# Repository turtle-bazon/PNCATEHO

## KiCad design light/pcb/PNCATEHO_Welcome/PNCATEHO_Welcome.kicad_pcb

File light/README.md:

# PNCATEHO

## PNCATEHO Welcome

### BOM

[IBOM](https://htmlpreview.github.io/?https://github.com/turtle-bazon/PNCATEHO/blob/master/light/ibom_welcome.html)

| Name               | Value          | Package                            | Quanity | JLC                                                                                    | Aliexpress                                                          | Misc                                                                                                                             |
| ------------------ | -------------- | :--------------------------------- | ------- | -------------------------------------------------------------------------------------- | ------------------------------------------------------------------- | -------------------------------------------------------------------------------------------------------------------------------- |
| Capacitor          | 1              | 0805                               | 11      | [JLCPCB](https://jlcpcb.com/partdetail/39123-0805B104K500NT/C38141)                    | [Aliexpress](https://aliexpress.ru/item/1005008523091680.html)      |                                                                                                                                  |
| Capacitor          | 1uF            | 0805                               | 4       | [JLCPCB](https://jlcpcb.com/partdetail/29074-CL21B105KBFNNNE/C28323)                   | [Aliexpress](https://aliexpress.ru/item/1005008523091680.html)      |                                                                                                                                  |
| Capacitor          | 20pF           | 0805                               | 2       | [JLCPCB](https://jlcpcb.com/partdetail/KEMET-C0402C200K4GAC7867/C3839897)              | [Aliexpress](https://aliexpress.ru/item/1005008523091680.html)      |                                                                                                                                  |
| Resitor            | 1k             | 0805                               | 4       | [JLCPCB](https://jlcpcb.com/partdetail/VO-0805_1_1K/C2889437)                          | [Aliexpress](https://aliexpress.ru/item/1005004542788613.html)<br>  |                                                                                                                                  |
| Resitor            | 5.1k           | 0805                               | 2       | [JLCPCB](https://jlcpcb.com/partdetail/C5123602)                                       | [Aliexpress](https://aliexpress.ru/item/1005004542788613.html)<br>  |                                                                                                                                  |
| Resitor            | 27Ω            | 0805                               | 2       | [JLCPCB](https://jlcpcb.com/partdetail/YAGEO-AC0805FR7W27RL/C5120098)                  | [Aliexpress](https://aliexpress.ru/item/1005004542788613.html)<br>  |                                                                                                                                  |
| Resitor            | 10k            | 0805                               | 1       | [JLCPCB](https://jlcpcb.com/partdetail/VO-0805_1_10K/C2889436)                         | [Aliexpress](https://aliexpress.ru/item/1005004542788613.html)<br>  |                                                                                                                                  |
| LED                | Red            | 0805                               | 1       | [JLCPCB](https://jlcpcb.com/partdetail/85425-NCD0805R1/C84256)                         | [Aliexpress](https://aliexpress.ru/item/4000936781234.html)         |                                                                                                                                  |
| LED                | Blue           | 0805                               | 1       | [JLCPCB](https://jlcpcb.com/partdetail/Hubei_KentoElec-C2293/C2293)                    | [Aliexpress](https://aliexpress.ru/item/4000936781234.html)         |                                                                                                                                  |
| LED                | WS2812B        | 2020                               | 20      | [JLCPCB](https://jlcpcb.com/partdetail/Worldsemi-WS2812B2020/C965555)                  | [Aliexpress](https://aliexpress.ru/item/1005005812058130.html)<br>  |                                                                                                                                  |
| LDO                | RT9013-33GB    | SOT23-5                            | 1       | [JLCPCB](https://jlcpcb.com/partdetail/RichtekTech-RT901333GB/C47773)                  | [Aliexpress](https://aliexpress.ru/item/1005009379057215.html)<br>  |                                                                                                                                  |
| FLASH              | W25Q32JVSSIQ   | SOIC-8-208mil                      | 1       | [JLCPCB](https://jlcpcb.com/partdetail/WinbondElec-W25Q32JVSSIQ/C179173)<br>           | [Aliexpress](https://ali.click/ja3ym8)                              |                                                                                                                                  |
| ESD                | USBLC6-2SC6    | SOT23-6                            | 1       | [JLCPCB](https://jlcpcb.com/partdetail/STMicroelectronics-USBLC62SC6/C7519)<br>        | [Aliexpress](https://ali.click/vl3ymq)                              |                                                                                                                                  |
| Crystal            | 12MHz 20pF     | SMD3225-4P                         | 1       | [JLCPCB](https://jlcpcb.com/partdetail/YXC_CrystalOscillators-X322512MSB4SI/C9002)<br> | [Aliexpress](https://aliexpress.ru/item/1005006861125810.html)      |                                                                                                                                  |
| Fuse               | 500mA 6V       | 0805                               | 1       | [JLCPCB](https://jlcpcb.com/partdetail/BHFUSE-BSMD0805_0506V/C883108)<br>              | [Aliexpress](https://aliexpress.ru/item/1005009503064953.html)      |                                                                                                                                  |
| MCU                | RP2040         | LQFN-56(7x7)                       | 1       | [JLCPCB](https://jlcpcb.com/partdetail/RaspberryPi-RP2040/C2040)<br>                   | [Aliexpress](https://aliexpress.ru/item/1005007523217221.html?)     |                                                                                                                                  |
| Type-C             | TYPE-C-31-M-12 | 16P 5A Female                      | 1       | [JLCPCB](https://jlcpcb.com/partdetail/Korean_HropartsElec-TYPE_C_31_M12/C165948)<br>  | [Aliexpress](https://aliexpress.ru/item/1005005260008476.html?)<br> |                                                                                                                                  |
| Tactile Switch     | TS342A2P       | SMD 4x3mm                          | 2       | [JLCPCB](https://jlcpcb.com/partdetail/SHOUHAN-TS342A2P/C398055)                       | [Aliexpress](https://ali.click/1z4ym0l)<br>                         |                                                                                                                                  |
| Swtiches           | PG1316S        | SMD                                | 10      | [JLCPCB](https://jlcpcb.com/partdetail/Kailh-CPG1316S01D02/C42372112)<br>              |                                                                     | [Kailh](https://www.kailhswitch.com/mechanical-keyboard-switches/low-profile-key-switches/kailh-ultra-thin-notebook-switch.html) |
| Sockets (Optional) | PBS            | PH8.5                              | 10 pin  |                                                                                        | [Aliexpress](https://aliexpress.ru/item/1005001621924231.html)<br>  |                                                                                                                                  |
| Pin (Optional)     | PLS            |                                    | 10 Pin  |                                                                                        | [Aliexpress](https://aliexpress.ru/item/1005001708024520.html)<br>  |                                                                                                                                  |
| JST (Optional)     | SM10B-GHS-TB   | P=1.25mm,Surface Mount，Right Angle | 2       | [JLCPCB](https://jlcpcb.com/partdetail/JST-SM10B_GHSTB/C2683602)<br>                   | <br>                                                                | [ChipDip](https://www.chipdip.ru/product/sm10b-ghs-tb-connector-header-surface-mount-right-angle-jst-8033862895)                 |

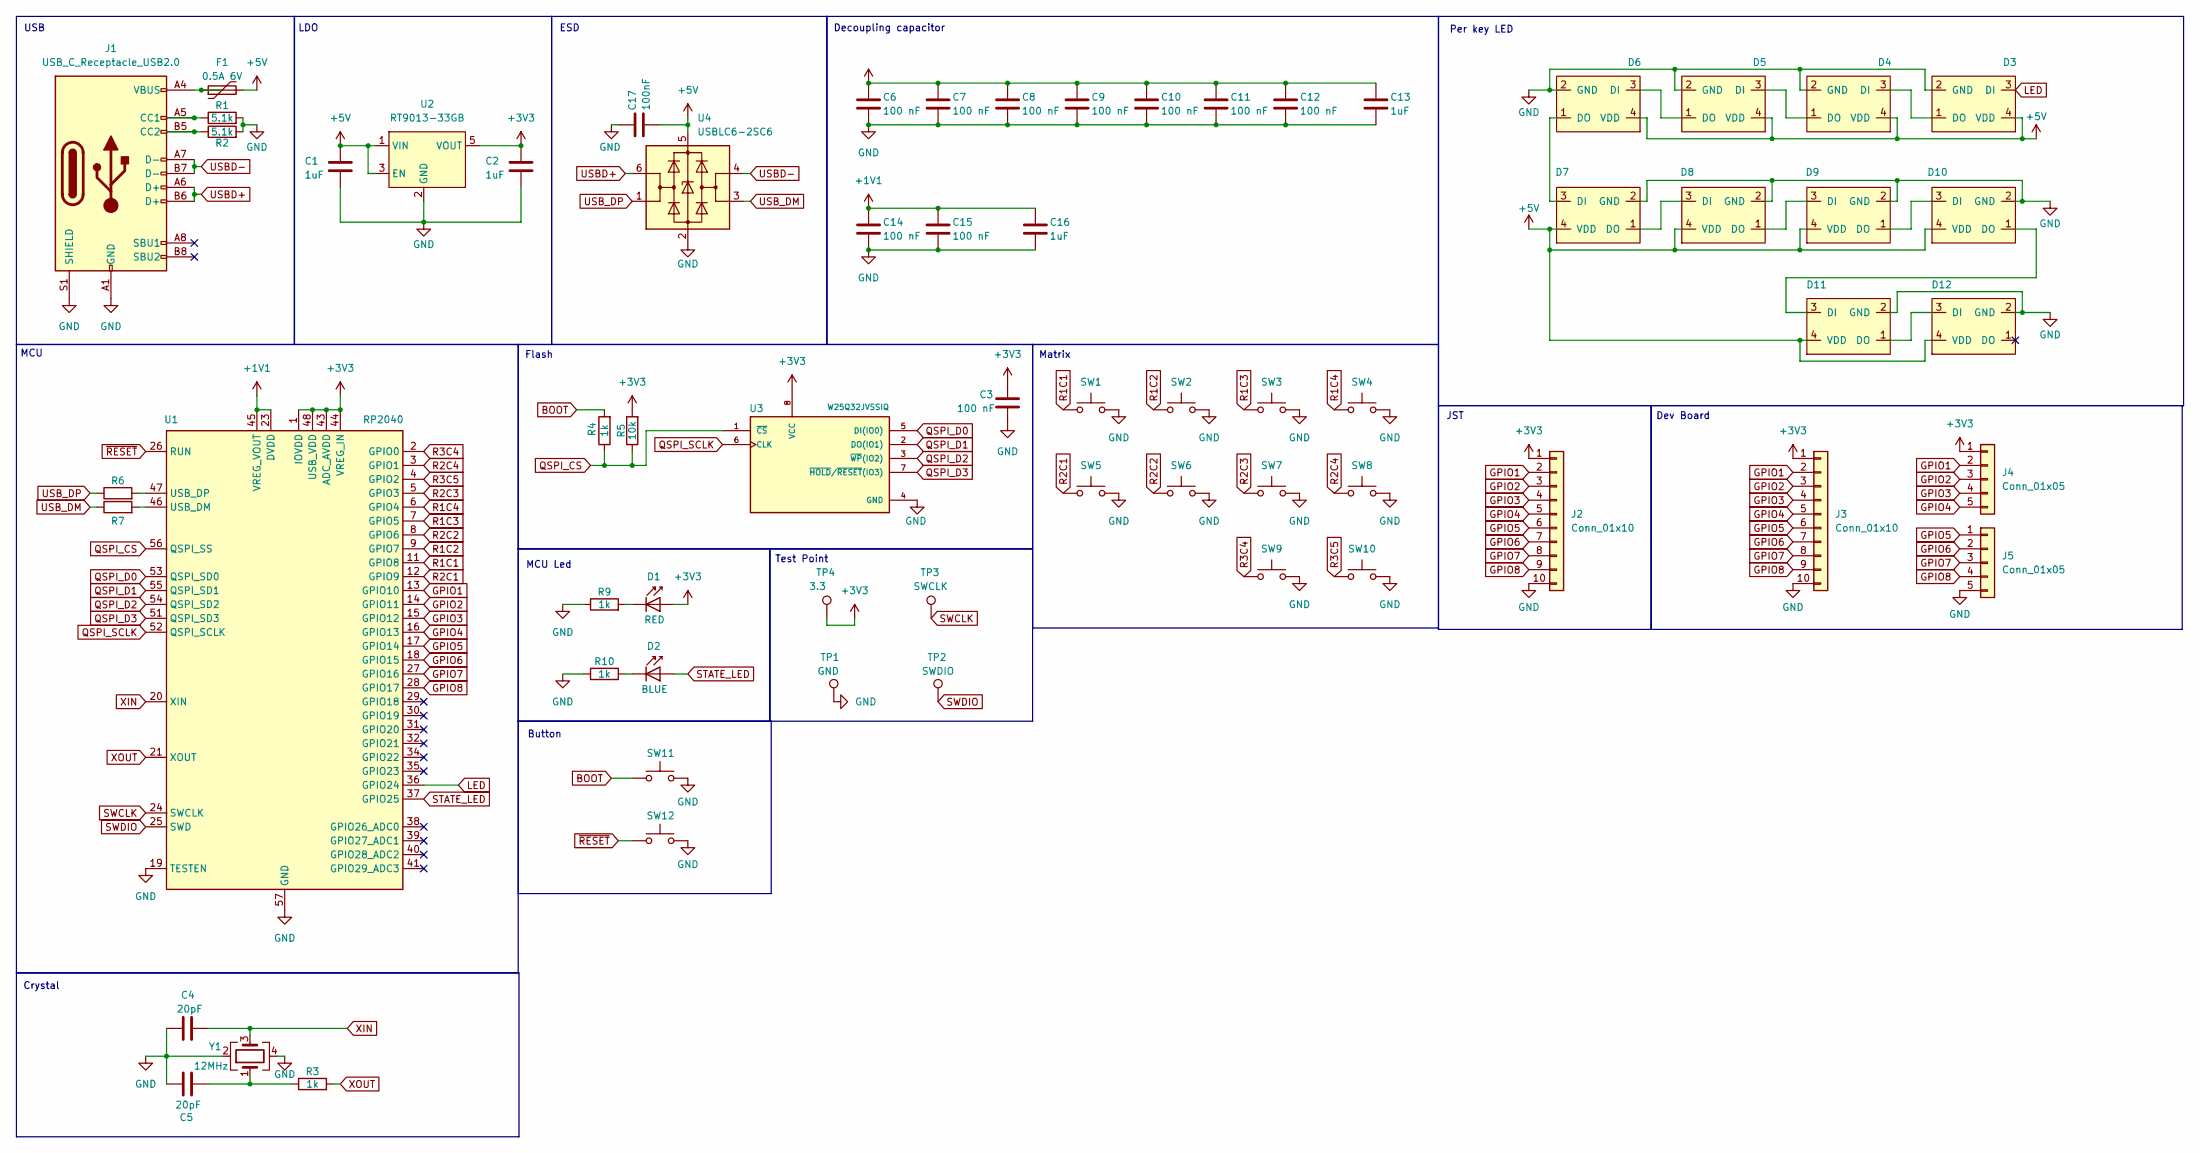
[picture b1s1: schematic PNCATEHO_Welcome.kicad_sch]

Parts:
C1, C2, C13, C16: 1uF; C_0805_2012Metric_Pad1.18x1.45mm_HandSolder
C3, C6, C7, C8, C9, C10, C11, C12, C14, C15: 100 nF; C_0805_2012Metric_Pad1.18x1.45mm_HandSolder
C4, C5: 20pF; C_0805_2012Metric_Pad1.18x1.45mm_HandSolder
C17: 100nF; C_0805_2012Metric_Pad1.18x1.45mm_HandSolder
D1: RED; LED_0805_2012Metric_Pad1.15x1.40mm_HandSolder
D2: BLUE; LED_0805_2012Metric_Pad1.15x1.40mm_HandSolder
D3, D4, D5, D6, D7, D8, D9, D10, D11, D12: WS2812-2020-2.00mmx2.20mm
F1: 0.5А 6V; Fuse_0805_2012Metric_Pad1.15x1.40mm_HandSolder
J1: USB_C_Receptacle_USB2.0; USB_C_Receptacle_TYPE-C-31-M-12
J2, J3: Conn_01x10; JST_GH_SM10B-GHS-TB_1x10-1MP_P1.25mm_Horizontal
J4, J5: Conn_01x05; PinHeader_1x05_P2.54mm_Vertical
R1, R2: 5.1k; R_0805_2012Metric_Pad1.20x1.40mm_HandSolder
R3, R4, R9, R10: 1k; R_0805_2012Metric_Pad1.20x1.40mm_HandSolder
R5: 10k; R_0805_2012Metric_Pad1.20x1.40mm_HandSolder
R6, R7: 27; R_0805_2012Metric_Pad1.20x1.40mm_HandSolder
SW1, SW2, SW3, SW4, SW5, SW6, SW7, SW8, SW9, SW10: SW_PG1316
SW11: Boot; SW_PUSH
SW12: Reset; SW_PUSH
TP1: GND; TestPoint_Pad_1.0x1.0mm
TP2: SWDIO; TestPoint_Pad_D1.0mm
TP3: SWCLK; TestPoint_Pad_D1.0mm
TP4: 3.3; TestPoint_Pad_D1.0mm
U1: RP2040; QFN-56-1EP_7x7mm_P0.4mm_EP3.2x3.2mm_ThermalVias
U2: RT9013-33GB; SOT-23-5_HandSoldering
U3: W25Q32JVSSIQ; SOIC-8_5.3x5.3mm_P1.27mm; M_PART_NUMBER W25QXX
U4: USBLC6-2SC6; SOT-23-6_Handsoldering
Y1: 12MHz; Crystal_SMD_3225-4Pin_3.2x2.5mm_HandSoldering

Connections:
+1V1: C14.1, C15.1, C16.1, U1.23 (DVDD), U1.45 (VREG_VOUT), U1.50 (DVDD)
+3V3: C2.1, C3.1, C6.1, C7.1, C8.1, C9.1, C10.1, C11.1, C12.1, C13.1, D1.2 (A), J2.1, J3.1, J4.1, R5.2, TP4.1, U1.1 (IOVDD), U1.10 (IOVDD), U1.22 (IOVDD), U1.33 (IOVDD), U1.42 (IOVDD), U1.43 (ADC_AVDD), U1.44 (VREG_IN), U1.48 (USB_VDD), U1.49 (IOVDD), U2.5 (VOUT), U3.8 (VCC)
+5V: C1.1, C17.2, D3.4 (VDD), D4.4 (VDD), D5.4 (VDD), D6.4 (VDD), D7.4 (VDD), D8.4 (VDD), D9.4 (VDD), D10.4 (VDD), D11.4 (VDD), D12.4 (VDD), F1.2, U2.1 (VIN), U2.3 (EN), U4.5 (VBUS)
BOOT: R4.2, SW11.2
GND: C1.2, C2.2, C3.2, C4.2, C5.2, C6.2, C7.2, C8.2, C9.2, C10.2, C11.2, C12.2, C13.2, C14.2, C15.2, C16.2, C17.1, D3.2 (GND), D4.2 (GND), D5.2 (GND), D6.2 (GND), D7.2 (GND), D8.2 (GND), D9.2 (GND), D10.2 (GND), D11.2 (GND), D12.2 (GND), J1.A1 (GND), J1.A12 (GND), J1.B1 (GND), J1.B12 (GND), J1.S1 (SHIELD), J2.10, J3.10, J5.5, R1.2, R2.2, R9.1, R10.1, SW1.2, SW2.2, SW3.2, SW4.2, SW5.2, SW6.2, SW7.2, SW8.2, SW9.2, SW10.2, SW11.1, SW12.1, TP1.1, U1.19 (TESTEN), U1.57 (GND), U2.2 (GND), U3.4 (GND), U4.2 (GND), Y1.2, Y1.4
GPIO1: J2.2, J3.2, J4.2, U1.13 (GPIO10)
GPIO2: J2.3, J3.3, J4.3, U1.14 (GPIO11)
GPIO3: J2.4, J3.4, J4.4, U1.15 (GPIO12)
GPIO4: J2.5, J3.5, J4.5, U1.16 (GPIO13)
GPIO5: J2.6, J3.6, J5.1, U1.17 (GPIO14)
GPIO6: J2.7, J3.7, J5.2, U1.18 (GPIO15)
GPIO7: J2.8, J3.8, J5.3, U1.27 (GPIO16)
GPIO8: J2.9, J3.9, J5.4, U1.28 (GPIO17)
LED: D3.3 (DI), U1.36 (GPIO24)
unnamed: C5.1, R3.1, Y1.1
unnamed: D1.1 (K), R9.2
unnamed: D2.1 (K), R10.2
unnamed: D3.1 (DO), D4.3 (DI)
unnamed: D4.1 (DO), D5.3 (DI)
unnamed: D5.1 (DO), D6.3 (DI)
unnamed: D6.1 (DO), D7.3 (DI)
unnamed: D7.1 (DO), D8.3 (DI)
unnamed: D8.1 (DO), D9.3 (DI)
unnamed: D9.1 (DO), D10.3 (DI)
unnamed: D10.1 (DO), D11.3 (DI)
unnamed: D11.1 (DO), D12.3 (DI)
unnamed: F1.1, J1.A4 (VBUS), J1.A9 (VBUS), J1.B4 (VBUS), J1.B9 (VBUS)
unnamed: J1.A5 (CC1), R1.1
unnamed: J1.B5 (CC2), R2.1
unnamed: R7.2, U1.46 (USB_DM)
unnamed: R6.2, U1.47 (USB_DP)
QSPI_CS: R4.1, R5.1, U1.56 (QSPI_SS), U3.1 (~CS)
QSPI_D0: U1.53 (QSPI_SD0), U3.5 (DI(IO0))
QSPI_D1: U1.55 (QSPI_SD1), U3.2 (DO(IO1))
QSPI_D2: U1.54 (QSPI_SD2), U3.3 (~WP(IO2))
QSPI_D3: U1.51 (QSPI_SD3), U3.7 (~HOLD/~RESET(IO3))
QSPI_SCLK: U1.52 (QSPI_SCLK), U3.6 (CLK)
R1C1: SW1.1, U1.11 (GPIO8)
R1C2: SW2.1, U1.9 (GPIO7)
R1C3: SW3.1, U1.7 (GPIO5)
R1C4: SW4.1, U1.6 (GPIO4)
R2C1: SW5.1, U1.12 (GPIO9)
R2C2: SW6.1, U1.8 (GPIO6)
R2C3: SW7.1, U1.5 (GPIO3)
R2C4: SW8.1, U1.3 (GPIO1)
R3C4: SW9.1, U1.2 (GPIO0)
R3C5: SW10.1, U1.4 (GPIO2)
STATE_LED: D2.2 (A), U1.37 (GPIO25)
SWCLK: TP3.1, U1.24 (SWCLK)
SWDIO: TP2.1, U1.25 (SWD)
USBD+: J1.A6 (D+), J1.B6 (D+), U4.6 (I/O1)
USBD-: J1.A7 (D-), J1.B7 (D-), U4.4 (I/O2)
USB_DM: R7.1, U4.3 (I/O2)
USB_DP: R6.1, U4.1 (I/O1)
XIN: C4.1, U1.20 (XIN), Y1.3
XOUT: R3.2, U1.21 (XOUT)
~RESET: SW12.2, U1.26 (RUN)

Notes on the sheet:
ESD
Test Point
Per key LED
MCU Led
Dev Board
Crystal
USB
MCU
Flash
LDO
Decoupling capacitor
JST
Button
Matrix

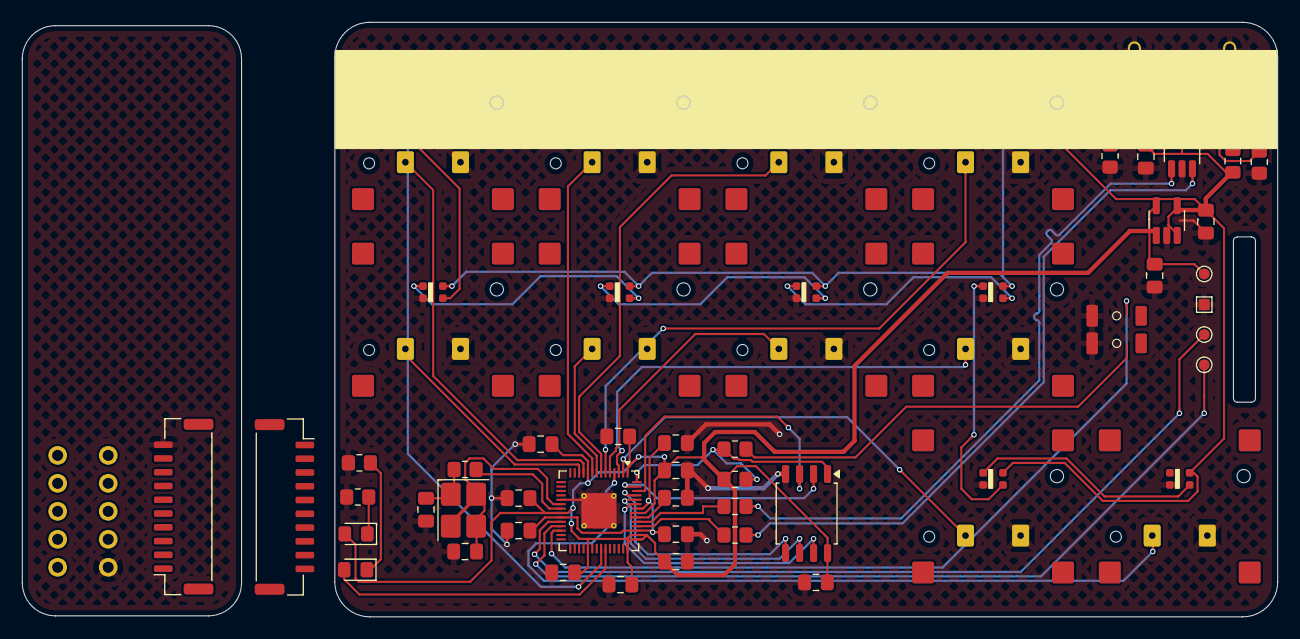
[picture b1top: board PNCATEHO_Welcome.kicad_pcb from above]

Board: 2 copper layers, 85.6 x 54.0 mm, 65 parts (0 on the bottom side), 57 nets.

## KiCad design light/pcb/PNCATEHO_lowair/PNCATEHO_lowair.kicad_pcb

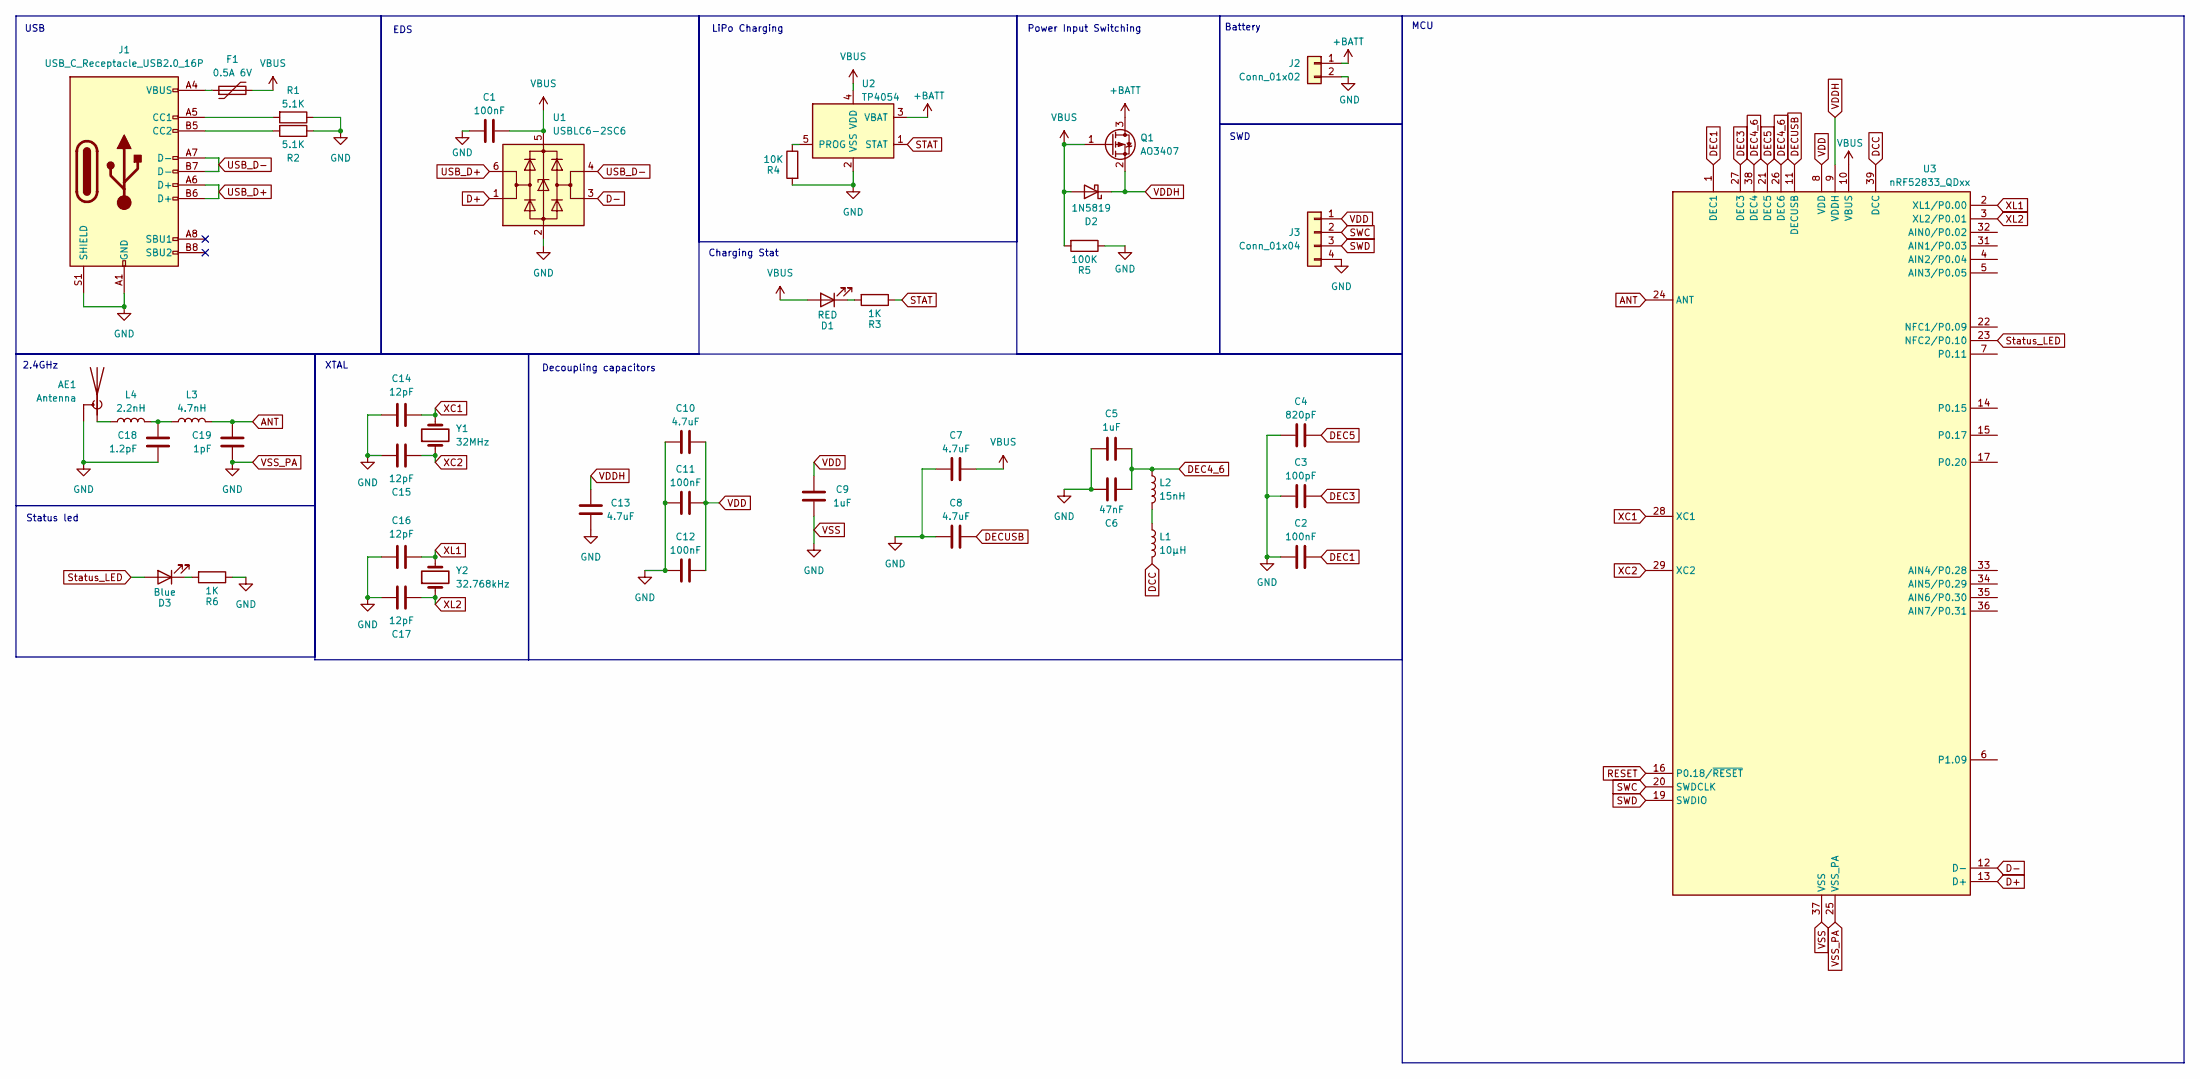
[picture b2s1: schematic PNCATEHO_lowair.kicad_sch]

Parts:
AE1: Antenna; Texas_SWRA117D_2.4GHz_Left
C1, C2, C11, C12: 100nF; C_0201_0603Metric_Pad0.64x0.40mm_HandSolder
C3: 100pF; C_0201_0603Metric_Pad0.64x0.40mm_HandSolder
C4: 820pF; C_0201_0603Metric_Pad0.64x0.40mm_HandSolder
C5, C9: 1uF; C_0402_1005Metric_Pad0.74x0.62mm_HandSolder
C6: 47nF; C_0201_0603Metric_Pad0.64x0.40mm_HandSolder
C7, C8, C10, C13: 4.7uF; C_0603_1608Metric_Pad1.08x0.95mm_HandSolder
C14, C15, C16, C17: 12pF; C_0201_0603Metric_Pad0.64x0.40mm_HandSolder
C18: 1.2pF; C_0201_0603Metric_Pad0.64x0.40mm_HandSolder
C19: 1pF; C_0201_0603Metric_Pad0.64x0.40mm_HandSolder
D1: RED; LED_0805_2012Metric_Pad1.15x1.40mm_HandSolder
D2: 1N5819; D_SOD-323_HandSoldering
D3: Blue; LED_0805_2012Metric_Pad1.15x1.40mm_HandSolder
F1: 0.5А 6V; Fuse_1206_3216Metric_Pad1.42x1.75mm_HandSolder
J1: USB_C_Receptacle_USB2.0_16P; USB_C_Receptacle_TYPE-C-31-M-12
J2: Conn_01x02
J3: Conn_01x04; connector_swd_REV
L1: 10μH; L_0603_1608Metric_Pad1.05x0.95mm_HandSolder
L2: 15nH; L_0402_1005Metric_Pad0.77x0.64mm_HandSolder
L3: 4.7nH; L_0201_0603Metric_Pad0.64x0.40mm_HandSolder
L4: 2.2nH; L_0201_0603Metric_Pad0.64x0.40mm_HandSolder
Q1: AO3407; SOT-23
R1, R2: 5.1K; R_0603_1608Metric_Pad0.98x0.95mm_HandSolder
R3, R6: 1K; R_0603_1608Metric_Pad0.98x0.95mm_HandSolder
R4: 10K; R_0603_1608Metric_Pad0.98x0.95mm_HandSolder
R5: 100K; R_0603_1608Metric_Pad0.98x0.95mm_HandSolder
U1: USBLC6-2SC6; SOT-23-6
U2: TP4054; SOT-23-5
U3: nRF52833_QDxx; QFN-40-1EP_5x5mm_P0.4mm_EP3.6x3.6mm_ThermalVias
Y1: 32MHz
Y2: 32.768kHz

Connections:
+BATT: J2.1, Q1.3 (D), U2.3 (VBAT)
ANT: C19.2, L3.1, U3.24 (ANT)
D+: U1.1 (I/O1), U3.13 (D+)
D-: U1.3 (I/O2), U3.12 (D-)
DCC: L1.2, U3.39 (DCC)
DEC1: C2.2, U3.1 (DEC1)
DEC3: C3.2, U3.27 (DEC3)
DEC4_6: C5.2, C6.2, L2.1, U3.26 (DEC6), U3.38 (DEC4)
DEC5: C4.2, U3.21 (DEC5)
DECUSB: C8.2, U3.11 (DECUSB)
unnamed: AE1.1 (A), L4.2
unnamed: C18.1, L3.2, L4.1
unnamed: D1.1 (K), R3.2
unnamed: D3.1 (K), R6.2
unnamed: F1.1, J1.A4 (VBUS), J1.A9 (VBUS), J1.B4 (VBUS), J1.B9 (VBUS)
unnamed: J1.A5 (CC1), R1.2
unnamed: J1.B5 (CC2), R2.2
unnamed: L1.1, L2.2
unnamed: R4.1, U2.5 (PROG)
RESET: U3.16 (P0.18/~RESET)
STAT: R3.1, U2.1 (STAT)
SWC: J3.2, U3.20 (SWDCLK)
SWD: J3.3, U3.19 (SWDIO)
Status_LED: D3.2 (A), U3.23 (NFC2/P0.10)
USB_D+: J1.A6 (D+), J1.B6 (D+), U1.6 (I/O1)
USB_D-: J1.A7 (D-), J1.B7 (D-), U1.4 (I/O2)
VBUS: C1.2, C7.2, D1.2 (A), D2.2 (A), F1.2, Q1.1 (G), R5.2, U1.5 (VBUS), U2.4 (VDD), U3.10 (VBUS)
VDD: C9.1, C10.2, C11.2, C12.2, J3.1, U3.8 (VDD), U3.18 (VDD), U3.30 (VDD), U3.40 (VDD)
VDDH: C13.1, D2.1 (K), Q1.2 (S), U3.9 (VDDH)
VSS: AE1.2 (Shield), C1.1, C2.1, C3.1, C4.1, C5.1, C6.1, C7.1, C8.1, C9.2, C10.1, C11.1, C12.1, C13.2, C14.1, C15.2, C16.1, C17.2, C18.2, C19.1, J1.A1 (GND), J1.A12 (GND), J1.B1 (GND), J1.B12 (GND), J1.S1 (SHIELD), J2.2, J3.4, R1.1, R2.1, R4.2, R5.1, R6.1, U1.2 (GND), U2.2 (VSS), U3.25 (VSS_PA), U3.37 (VSS), U3.41 (VSS)
XC1: C14.2, U3.28 (XC1), Y1.2
XC2: C15.1, U3.29 (XC2), Y1.1
XL1: C16.2, U3.2 (XL1/P0.00), Y2.2
XL2: C17.1, U3.3 (XL2/P0.01), Y2.1

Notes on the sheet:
EDS
Status led
Power Input Switching
USB
LiPo Charging
XTAL
2.4GHz
Charging Stat
SWD
Battery
Decoupling capacitors
MCU

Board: 2 copper layers, 40 parts (0 on the bottom side), 33 nets, no tracks yet.

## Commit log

2025-08-20 upload sheme
2025-08-21 PGS1316s PNCATEHO basic routing
2025-08-21 update routin
2025-08-21 update silkscreen
2025-08-21 update solid
2025-08-21 update step
2025-08-21 fix footprint
2025-08-22 upload ibom
2025-08-22 update outline
2025-08-24 Change default Silicone Pad Diameter to 8mm
2025-08-24 Some little fixes
2025-08-25 Add production files to ignore
2025-08-28 add esd protection
2025-08-28 add some fix
2025-08-28 remove reset button
2025-08-28 change design
2025-08-28 remove led
2025-08-28 add button
2025-08-29 * components moved closer to each other; * rerouted with esd protection; * fixed usb data differential pair length; * changed design to be like a credit card;
2025-08-29 update design
2025-08-29 Tune differential pair (USB data) lengths
2025-09-02 rename project
2025-09-02 clear sch
2025-09-09 fix silc
2025-09-09 add led
2025-09-10 fix sh
2025-09-20 PNCATEHO Welcome RGB routing
2025-09-22 Return state led to GPIO25
2025-10-17 upload lowair source
2025-10-20 JST1.25 footprint
2025-10-20 update footprint
2025-10-20 update scheme
2025-10-24 update sh
2025-10-24 update footpint
2025-10-24 update pcb
2025-10-24 generate ibom
2025-10-24 updare light era README
2025-10-24 add BOM
2025-10-24 update BOM
